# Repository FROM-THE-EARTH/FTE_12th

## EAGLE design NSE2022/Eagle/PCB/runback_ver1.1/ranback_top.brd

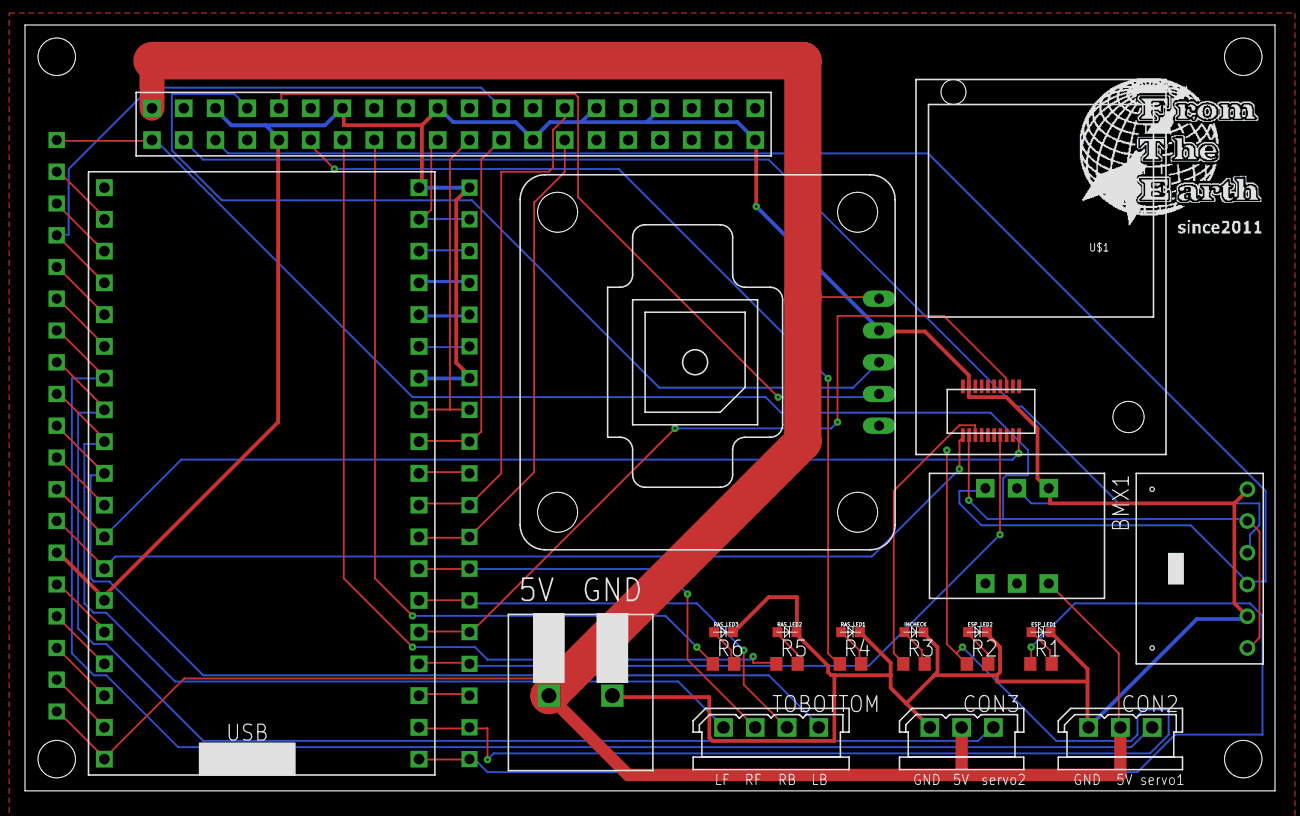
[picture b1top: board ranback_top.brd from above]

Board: 2 copper layers, 100.0 x 61.3 mm, 25 parts (0 on the bottom side), 50 nets.

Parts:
BMX1: BMX055
CON2, CON3: 2.5_MINI-SPOX_3PIN
ESP_LED1, ESP_LED2: OSXX1608C1A
GPS: AE-GYSFDMAXB
IM: IM920C
IMCHECK: OSXX1608C1A
PIN_L: 19_2.54
PIN_R: 19_2.54
R1, R2, R3, R4, R5, R6: 1.5k; R0603
RASPBERRYPI_4B: RASPBERRYPI4B
RAS_LED1, RAS_LED2, RAS_LED3: OSXX1608C1A
TM5: TERMINAL_SLOPED_2PIN
TOBOTTOM: 2.5_MINI-SPOX_4PIN
U$1: LOGO
U$2: ESP32
U$9: GY-BPM280; GY-BMP280-FOOTPRINT

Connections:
+3V3: IM.$P17, PIN_L.1, RASPBERRYPI_4B.3V3_1, U$9.CSB, U$9.VCC
+5V: BMX1.VCC, CON2.2, CON3.2, GPS.P1, PIN_L.19, RASPBERRYPI_4B.5V_1, TM5.1, U$2.5V
BB_SCL: BMX1.SCL, RASPBERRYPI_4B.GPIO3, U$9.SCK
BB_SDA: BMX1.SDA, RASPBERRYPI_4B.GPIO2, U$9.SDI
EN: PIN_L.2, U$2.EN
GND: BMX1.GND, CON2.1, CON3.1, ESP_LED1.CT, ESP_LED2.CT, GPS.P2, IM.$P18, IMCHECK.CT, PIN_L.14, PIN_R.1, PIN_R.7, RASPBERRYPI_4B.GND_1, RASPBERRYPI_4B.GND_2, RASPBERRYPI_4B.GND_3, RASPBERRYPI_4B.GND_4, RASPBERRYPI_4B.GND_5, RASPBERRYPI_4B.GND_6, RASPBERRYPI_4B.GND_7, RASPBERRYPI_4B.GND_8, RAS_LED1.CT, RAS_LED2.CT, RAS_LED3.CT, TM5.2, U$2.GND1, U$2.GND2, U$2.GND3, U$9.GND, U$9.SDO
GPS_RX: GPS.P3, RASPBERRYPI_4B.GPIO14
GPS_TX: GPS.P4, RASPBERRYPI_4B.GPIO15
IM_BUSY: IM.$P1, PIN_L.12, U$2.GPIO14
IM_RESET: IM.$P19, PIN_L.13, U$2.GPIO12
IM_RX: IM.$P6, PIN_R.15, U$2.GPIO2
IM_TX: IM.$P7, PIN_R.16, U$2.GPIO15
IO5: PIN_R.10, U$2.GPIO5
IO8: PIN_R.17, U$2.GPIO8
IO9: PIN_L.16, U$2.GPIO9
IO10: PIN_L.17, U$2.GPIO10
IO11: PIN_L.18, U$2.GPIO11
IO13: PIN_L.15, U$2.GPIO13
IO27: PIN_L.11, U$2.GPIO27
IO34: PIN_L.5, U$2.GPIO34
IO35: PIN_L.6, U$2.GPIO35
LED1: PIN_R.19, R1.1, U$2.GPIO6
LED2: PIN_R.18, R2.1, U$2.GPIO7
LED3: IM.$P15, R3.1
LED4: R4.1, RASPBERRYPI_4B.GPIO17
LED5: R5.1, RASPBERRYPI_4B.GPIO27
LED6: R6.1, RASPBERRYPI_4B.GPIO22
MD_LB: PIN_L.10, TOBOTTOM.P$2, U$2.GPIO26
MD_LF: PIN_L.9, TOBOTTOM.P$1, U$2.GPIO25
MD_RB: PIN_R.14, TOBOTTOM.P$4, U$2.GPIO0
MD_RF: PIN_R.13, TOBOTTOM.P$3, U$2.GPIO4
unnamed: ESP_LED1.AN, R1.2
unnamed: ESP_LED2.AN, R2.2
unnamed: IMCHECK.AN, R3.2
unnamed: R4.2, RAS_LED1.AN
unnamed: R5.2, RAS_LED2.AN
unnamed: R6.2, RAS_LED3.AN
RP_MISO: PIN_R.8, RASPBERRYPI_4B.GPIO9, U$2.GPIO19
RP_MOSI: PIN_R.2, RASPBERRYPI_4B.GPIO10, U$2.GPIO23
RP_RX: PIN_R.11, RASPBERRYPI_4B.GPIO1, U$2.GPIO17
RP_SCK: PIN_R.9, RASPBERRYPI_4B.GPIO11, U$2.GPIO18
RP_SS: PIN_L.4, RASPBERRYPI_4B.GPIO8, U$2.GPIO39
RP_TX: PIN_R.12, RASPBERRYPI_4B.GPIO0, U$2.GPIO16
RXD: PIN_R.4, U$2.TX
SCL: PIN_R.3, U$2.GPIO22
SDA: PIN_R.6, U$2.GPIO21
SENSOR_VP: PIN_L.3, U$2.GPIO36
SERVO1: CON2.3, PIN_L.7, U$2.GPIO32
SERVO2: CON3.3, PIN_L.8, U$2.GPIO33
TXD: PIN_R.5, U$2.RX

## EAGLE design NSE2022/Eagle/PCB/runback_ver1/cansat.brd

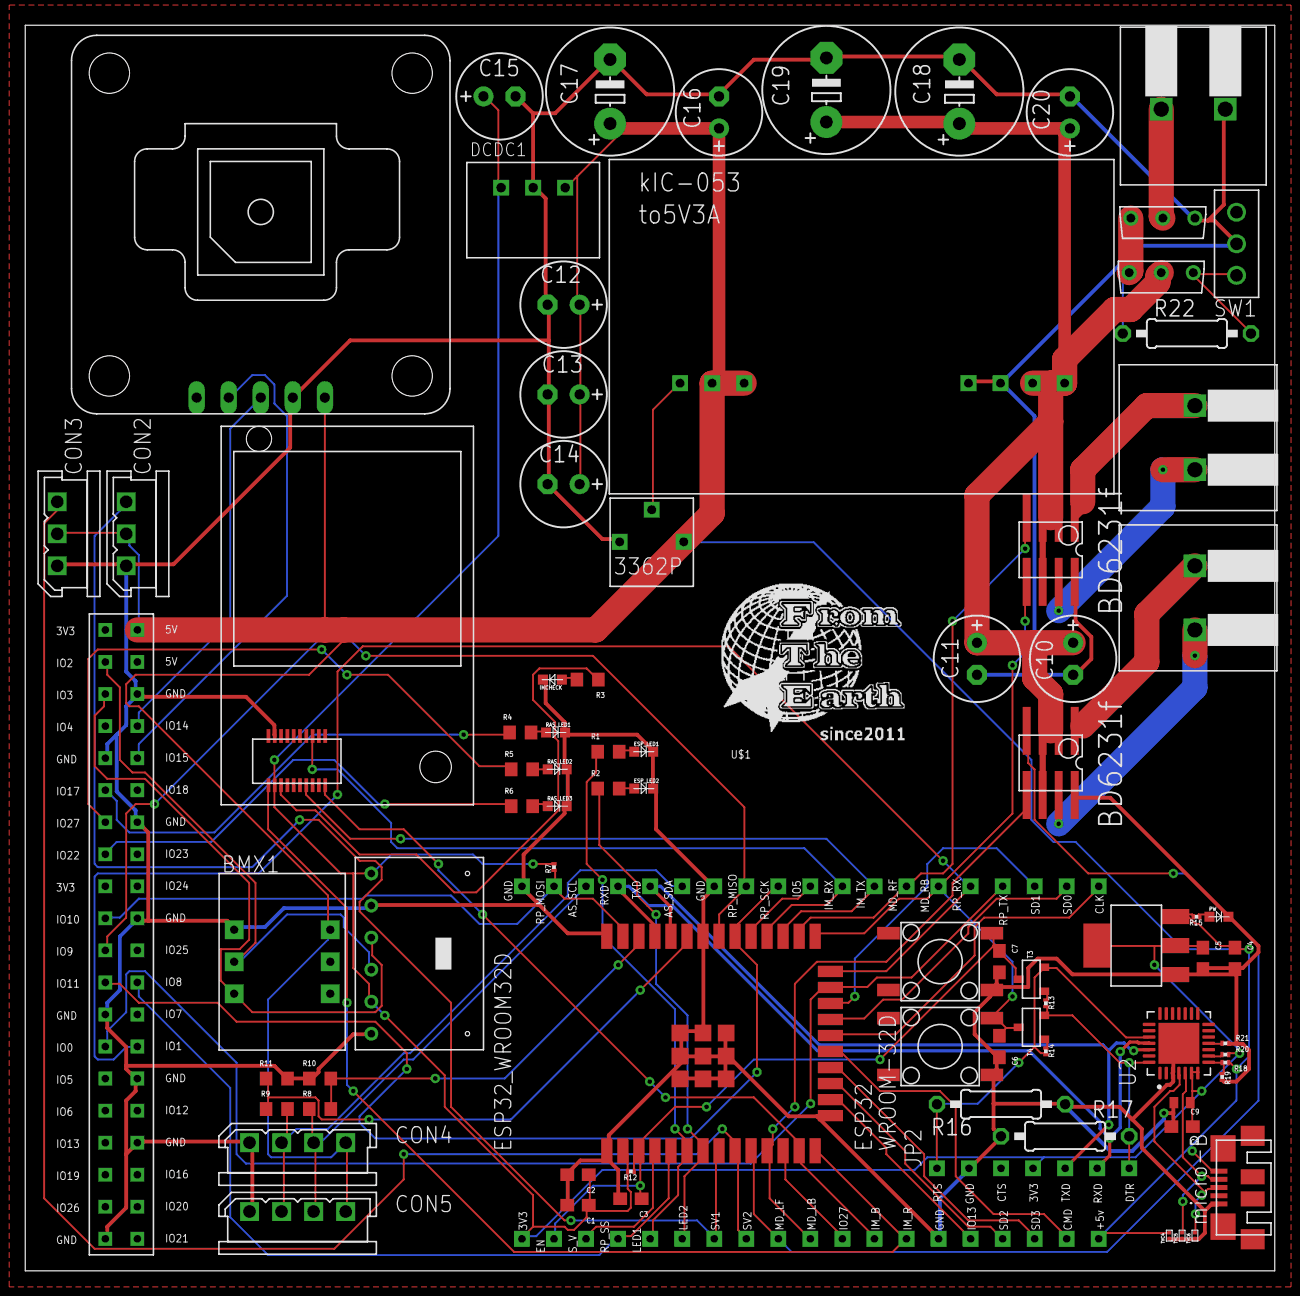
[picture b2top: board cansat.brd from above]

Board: 2 copper layers, 99.0 x 98.7 mm, 84 parts (0 on the bottom side), 71 nets.

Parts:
3-REG2: AZ1117CH-3.3TRG1
100KR1: 100kR; 3362P
BMX1: BMX055
C1: 22uF; C0603
C2, C3, C6, C7, C8: 0.1uF; C0603
C4, C5: 22uf; C0603
C9: 4.7uF; C0402
C10: 100uf; E2,5-7
C11: 0.1uf; E2,5-7
C12, C13, C14, C15: 4.7uF; E2,5-7
C16, C20: 0.1uF; E2,5-7
C17, C18, C19: 1000uF; E5-10,5
CON2, CON3: 2.5_MINI-SPOX_3PIN
CON4, CON5: 2.5_MINI-SPOX_4PIN
DCDC1: 5-3.3; 3.3V0.5A_M78AR05-0.5
EN1: TS-06104
ESP32_WROOM32D: ESP32-WROOM-32D
ESP_LED1, ESP_LED2: OSXX1608C1A
GPS: AE-GYSFDMAXB
IM: IM920C
IMCHECK: OSXX1608C1A
IO1: TS-06104
JP2: 7pin; 7_2.54
MD_L: BD6231F
MD_R: BD6231F
PIN_L: 19_2.54
PIN_R: 19_2.54
PW: OSXX1608C1A
R1, R2, R3, R4, R5, R6: 1.5k; R0603
R7, R12, R13, R14, R21: 10k; R0201
R8, R9: 2.2kR; R0603
R10, R11: 3.3kR; R0603
R15, R20: 2k; R0201
R16, R17: 100k; 0207/10
R18: 22k; R0201
R19: 47k; R0201
R22: 0207/10
RASPBERRYPI_4B: RASPBERRYPI4B
RAS_LED1, RAS_LED2, RAS_LED3: OSXX1608C1A
SW1: SRIDE_SWITCH
T3, T4: NPN_SS8050-G
TM1, TM2, TM3: TERMINAL_SLOPED_2PIN
TVC4, TVC5, TVC6: ESD5484FCT5G
U2: CP2102N-A01-GQFN28; QFN50P500X500X80-29N
U$1: LOGO
U$7, U$10: 2SJ681-PCH; 2SJ681
U$8: 5V3A_KIC-053
U$9: GY-BPM280; GY-BMP280-FOOTPRINT
USB2: MICRO-B_ZX62R-B-5P

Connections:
+3V3: 3-REG2.2, 3-REG2.VOUT, C1.1, C2.1, C5.1, C8.1, C9.1, C15.+, DCDC1.VOUT, ESP32_WROOM32D.2_3V3, IM.$P17, JP2.P$4, PIN_L.P$1, R7.2, R12.2, R20.1, U2.6, U2.7, U$9.CSB, U$9.VCC
+5V: 3-REG2.3, 100KR1.CCW, BMX1.VCC, C4.1, C12.+, C13.+, C14.+, C16.+, C17.+, CON2.2, CON3.2, CON4.P$2, CON5.P$2, DCDC1.VIN, GPS.P1, PIN_L.P$19, R15.2, R18.1, RASPBERRYPI_4B.5V_1, TVC4.2_AN, U$8.VOUT1, U$8.VOUT2, USB2.1
+12V: C10.+, C11.+, C18.+, C19.+, C20.+, MD_L.VCC1, MD_L.VCC2, MD_L.VREF, MD_R.VCC1, MD_R.VCC2, MD_R.VREF, U$8.VIN1, U$8.VIN2, U$10.DRAIN
+D: TVC6.2_AN, U2.4, USB2.3
-D: TVC5.2_AN, U2.5, USB2.2
A7_1: R22.2, U$7.SOURCE, U$10.SOURCE
AS_SCL: CON4.P$4, CON5.P$4, PIN_R.P$3, R8.2
AS_SDA: CON4.P$3, CON5.P$3, PIN_R.P$6, R9.2
BB_SCL: BMX1.SCL, RASPBERRYPI_4B.GPIO3, U$9.SCK
BB_SDA: BMX1.SDA, RASPBERRYPI_4B.GPIO2, U$9.SDI
CLK: ESP32_WROOM32D.20_CLK, PIN_R.P$19
CMD: ESP32_WROOM32D.19_CMD, PIN_L.P$18
CPVBUS: R18.2, R19.2, U2.8
DTR: JP2.P$7, R13.1, R17.2, T4.2, U2.28
EN: C3.1, C7.1, EN1.D, ESP32_WROOM32D.3_EN, PIN_L.P$2, R12.1, T3.3
GND: 3-REG2.1, 100KR1.CW, BMX1.GND, C1.2, C2.2, C3.2, C4.2, C5.2, C6.2, C7.2, C8.2, C9.2, C10.-, C11.-, C12.-, C13.-, C14.-, C15.-, C16.-, C17.-, C18.-, C19.-, C20.-, CON2.1, CON3.1, CON4.P$1, CON5.P$1, DCDC1.GND, EN1.B, ESP32_WROOM32D.1_GND, ESP32_WROOM32D.15_GND, ESP32_WROOM32D.32_NC, ESP32_WROOM32D.38_GND, ESP32_WROOM32D.GND@1, ESP32_WROOM32D.GND@2, ESP32_WROOM32D.GND@3, ESP32_WROOM32D.GND@4, ESP32_WROOM32D.GND@5, ESP32_WROOM32D.GND@6, ESP32_WROOM32D.GND@7, ESP32_WROOM32D.GND@8, ESP32_WROOM32D.GND@9, ESP_LED1.CT, ESP_LED2.CT, GPS.P2, IM.$P18, IMCHECK.CT, IO1.B, JP2.P$2, MD_L.GND, MD_R.GND, PIN_L.P$14, PIN_R.P$1, PIN_R.P$7, PW.CT, R10.1, R11.1, R16.1, R17.1, R19.1, R21.2, RASPBERRYPI_4B.GND_1, RASPBERRYPI_4B.GND_2, RASPBERRYPI_4B.GND_3, RASPBERRYPI_4B.GND_4, RASPBERRYPI_4B.GND_5, RASPBERRYPI_4B.GND_6, RASPBERRYPI_4B.GND_7, RASPBERRYPI_4B.GND_8, RAS_LED1.CT, RAS_LED2.CT, RAS_LED3.CT, SW1.LR, TM3.2, TVC4.1_CT, TVC5.1_CT, TVC6.1_CT, U2.3, U2.29, U$7.GATE, U$8.GND1, U$8.GND2, U$9.GND, U$9.SDO, USB2.5
GPS_RX: GPS.P3, RASPBERRYPI_4B.GPIO14
GPS_TX: GPS.P4, RASPBERRYPI_4B.GPIO15
IM_BUSY: ESP32_WROOM32D.13_IO14, IM.$P1, PIN_L.P$12
IM_RESET: ESP32_WROOM32D.14_IO12, IM.$P19, PIN_L.P$13
IM_RX: ESP32_WROOM32D.28_IO17, IM.$P6, PIN_R.P$11
IM_TX: ESP32_WROOM32D.27_IO16, IM.$P7, PIN_R.P$12
IO5: ESP32_WROOM32D.29_IO5, PIN_R.P$10
IO13: ESP32_WROOM32D.16_IO13, PIN_L.P$15
IO27: ESP32_WROOM32D.12_IO27, PIN_L.P$11
LED1: ESP32_WROOM32D.6_IO34, PIN_L.P$5, R1.1
LED2: ESP32_WROOM32D.7_IO35, PIN_L.P$6, R2.1
LED3: IM.$P15, R3.1
LED4: R4.1, RASPBERRYPI_4B.GPIO17
LED5: R5.1, RASPBERRYPI_4B.GPIO27
LED6: R6.1, RASPBERRYPI_4B.GPIO22
MD_LB: ESP32_WROOM32D.11_IO26, MD_L.RIN, PIN_L.P$10
MD_LF: ESP32_WROOM32D.10_IO25, MD_L.FIN, PIN_L.P$9
MD_RB: C6.1, ESP32_WROOM32D.25_IO0, IO1.D, MD_R.RIN, PIN_R.P$14, T4.3
MD_RF: ESP32_WROOM32D.26_IO4, MD_R.FIN, PIN_R.P$13
unnamed: ESP_LED1.AN, R1.2
unnamed: ESP_LED2.AN, R2.2
unnamed: IMCHECK.AN, R3.2
unnamed: R4.2, RAS_LED1.AN
unnamed: R5.2, RAS_LED2.AN
unnamed: R6.2, RAS_LED3.AN
unnamed: ESP32_WROOM32D.36_IO22, R8.1, R10.2
unnamed: ESP32_WROOM32D.33_IO21, R9.1, R11.2
unnamed: TM3.1, U$7.DRAIN
unnamed: PW.AN, R15.1
unnamed: R13.2, T3.1
unnamed: R14.2, T4.1
unnamed: R20.2, U2.9
unnamed: R21.1, U2.11
unnamed: 100KR1.WIPER, U$8.VADJ
unnamed: R22.1, SW1.L, U$10.GATE
OUT_MD_L1: MD_L.OUT1, TM2.1
OUT_MD_L2: MD_L.OUT2, TM2.2
OUT_MD_R1: MD_R.OUT1, TM1.1
OUT_MD_R2: MD_R.OUT2, TM1.2
RP_MISO: ESP32_WROOM32D.31_IO19, PIN_R.P$8, RASPBERRYPI_4B.GPIO9
RP_MOSI: ESP32_WROOM32D.37_IO23, PIN_R.P$2, R7.1, RASPBERRYPI_4B.GPIO10
RP_RX: ESP32_WROOM32D.24_IO2, PIN_R.P$15, RASPBERRYPI_4B.GPIO1
RP_SCK: ESP32_WROOM32D.30_IO18, PIN_R.P$9, RASPBERRYPI_4B.GPIO11
RP_SS: ESP32_WROOM32D.5_SENSOR_VN, PIN_L.P$4, RASPBERRYPI_4B.GPIO8
RP_TX: ESP32_WROOM32D.23_IO15, PIN_R.P$16, RASPBERRYPI_4B.GPIO0
RTS: JP2.P$1, R14.1, R16.2, T3.2, U2.24
RXD: ESP32_WROOM32D.35_TXD0, JP2.P$6, PIN_R.P$4, U2.25
SD0: ESP32_WROOM32D.21_SD0, PIN_R.P$18
SD1: ESP32_WROOM32D.22_SD1, PIN_R.P$17
SD2: ESP32_WROOM32D.17_SD2, PIN_L.P$16
SD3: ESP32_WROOM32D.18_SD3, PIN_L.P$17
SENSOR_VP: ESP32_WROOM32D.4_SENSOR_VP, PIN_L.P$3
SERVO1: CON2.3, ESP32_WROOM32D.8_IO32, PIN_L.P$7
SERVO2: CON3.3, ESP32_WROOM32D.9_IO33, PIN_L.P$8
TXD: ESP32_WROOM32D.34_RXD0, JP2.P$5, PIN_R.P$5, U2.26

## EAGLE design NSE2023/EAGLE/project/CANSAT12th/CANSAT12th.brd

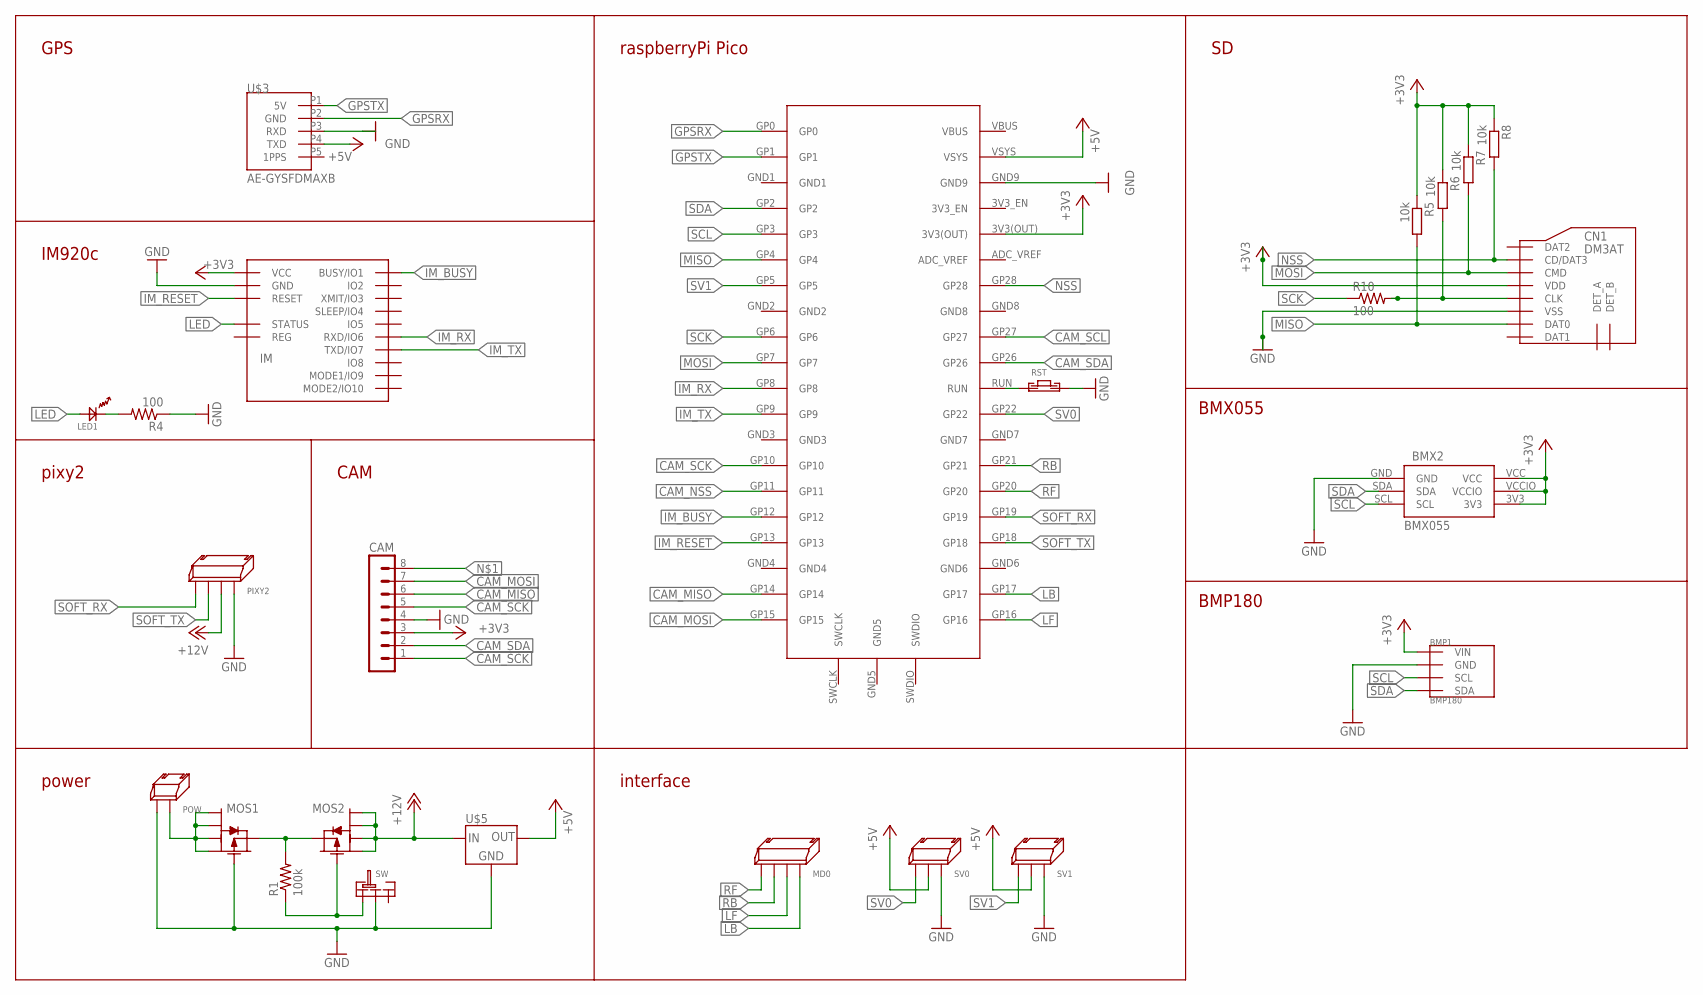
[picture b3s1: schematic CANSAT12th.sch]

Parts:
BMP1: BMP180; GY-68
BMX2: BMX055
CAM: MA08-1
CN1: DM3AT
IM: IM920C
LED1: OSXX1608C1A
MD0: 4PIN_SIDE
MOS1, MOS2: PCH_SSM6J808R; SSM6J808R
PIXY2: 4PIN_SIDE
POW: 2PIN_SIDE
R1: 100k; R0603
R4, R10: 100; R0603
R5, R6, R7, R8: 10k; R0603
RST: TVAF06-A020B-R
SV0, SV1: 3PIN_SIDE
SW: SRIDE_SWITCH
U$1: RASPBERRYPIPICO
U$3: AE-GYSFDMAXB
U$5: LT1117-5; SOT-223

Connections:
+3V3: BMP1.P1 (VIN), BMX2.3V3, BMX2.VCC, BMX2.VCCIO, CAM.3, CN1.VDD, IM.$P17 (VCC), R5.1, R6.1, R7.1, R8.1, U$1.3V3(OUT)
+5V: SV0.P$1, SV1.P$1, U$1.VSYS, U$3.P4 (TXD), U$5.2 (OUT)
+12V: MOS2.1, MOS2.2, MOS2.5, MOS2.6, PIXY2.P$3, U$5.3 (IN)
CAM_MISO: CAM.6, U$1.GP14
CAM_MOSI: CAM.7, U$1.GP15
CAM_NSS: U$1.GP11
CAM_SCK: CAM.1, CAM.5, U$1.GP10
CAM_SCL: U$1.GP27
CAM_SDA: CAM.2, U$1.GP26
GND: BMP1.P2 (GND), BMX2.GND, CAM.4, CN1.VSS, IM.$P18 (GND), MOS1.3, PIXY2.P$4, POW.P$2, R4.1, RST.P$2, SV0.P$3, SV1.P$3, SW.LR, U$5.4 (GND)
GND1: U$3.P3 (RXD)
GPSRX: U$1.GP0, U$3.P2 (GND)
GPSTX: U$1.GP1, U$3.P1 (5V)
IM_BUSY: IM.$P1 (BUSY/IO1), U$1.GP12
IM_RESET: IM.$P19 (RESET), U$1.GP13
IM_RX: IM.$P6 (RXD/IO6), U$1.GP8
IM_TX: IM.$P7 (TXD/IO7), U$1.GP9
LB: MD0.P$4, U$1.GP17
LED: IM.$P15 (STATUS), LED1.AN
LF: MD0.P$3, U$1.GP16
MISO: CN1.DAT0, R5.2, U$1.GP4
MOSI: CN1.CMD, R7.2, U$1.GP7
unnamed: RST.P$1, U$1.RUN
unnamed: LED1.CT, R4.2
unnamed: MOS1.4, MOS2.4, R1.2
unnamed: MOS2.3, R1.1, SW.L
unnamed: MOS1.1, MOS1.2, MOS1.5, MOS1.6, POW.P$1
NSS: CN1.CD/DAT3, R8.2, U$1.GP28
RB: MD0.P$1, U$1.GP21
RF: MD0.P$2, U$1.GP20
SCK: CN1.CLK, R6.2, R10.1, R10.2, U$1.GP6
SCL: BMP1.P3 (SCL), BMX2.SCL, U$1.GP3
SDA: BMP1.P4 (SDA), BMX2.SDA, U$1.GP2
SOFT_RX: PIXY2.P$2, U$1.GP19
SOFT_TX: PIXY2.P$1, U$1.GP18
SV0: SV0.P$2, U$1.GP22
SV1: SV1.P$2, U$1.GP5

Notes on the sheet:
BMP180
BMX055
raspberryPi Pico
GPS
IM920c
pixy2
CAM
power
interface

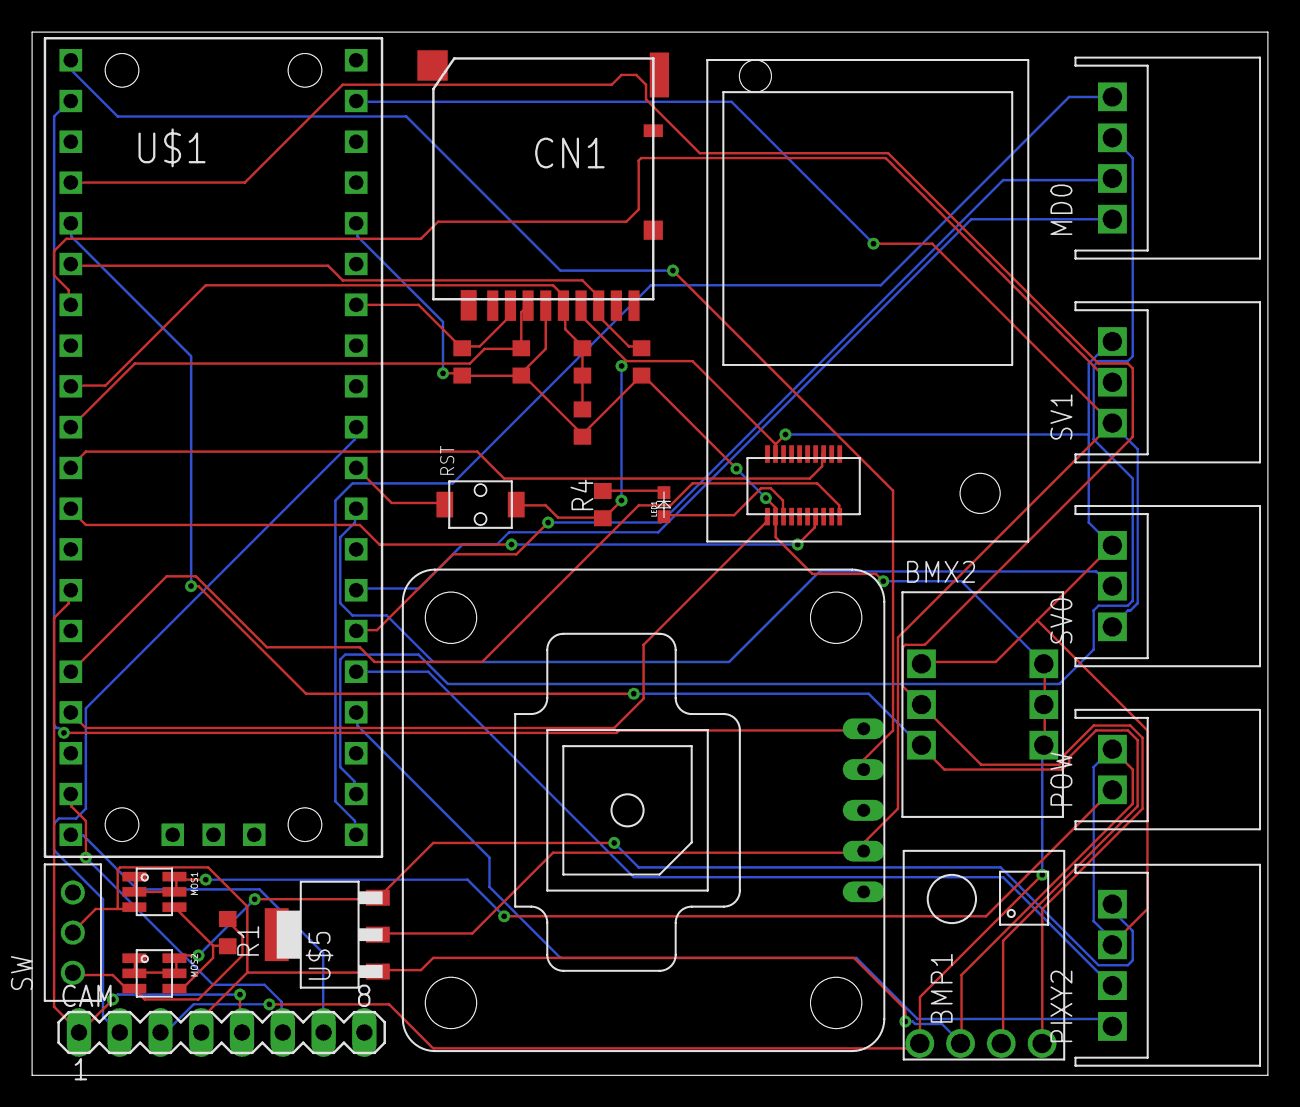
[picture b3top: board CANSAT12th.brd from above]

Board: 2 copper layers, 77.0 x 65.0 mm, 25 parts (0 on the bottom side), 34 nets.

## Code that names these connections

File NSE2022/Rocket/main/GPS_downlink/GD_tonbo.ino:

#include<TinyGPS++.h>
#include<CAN.h>

#include "FS.h"
#include "SD.h"
#include "SPI.h"

TinyGPSPlus gps;
HardwareSerial Serial4(1);
HardwareSerial im920(2);

#define LED1 13
#define LED2 9
#define LED3 10

#define FLIGHT_PIN 32

union BIF {
  uint8_t b[4];
  int i;
  float f;
};

BIF norm;
BIF main_phase;
BIF Altitude;
BIF maxAltitude;
BIF main_val;


const int GPS_RX = 15;
const int GPS_TX = 2;

char buf_lat[20];
char buf_lon[20];

char buf_norm[20];
char buf_Altitude[20];
char buf_maxAltitude[20];
char buf_val[5];
char buf_phase[5];
char buf_time[20];

char logdata[60];
char senddata[40];

double longtitude = 0;
double latitude = 0;

int phase = 0;
int val = 1;
int launchedTime = 0;

bool init_SD = false;
char fileName[16];
int fileNum = 0;

void setup() {

  Serial.begin(115200);
  Serial4.begin(9600, SERIAL_8N1, 2, 15);
  pinMode(FLIGHT_PIN, INPUT);
  im920.begin(19200);
  im920.print("ECIO\r\n");

  CAN.setPins(27, 26);

  if (!CAN.begin(500E3)) {
    Serial.println("Starting CAN failed!");
    int timer = millis();
    while (1) {
      if (millis() - timer > 1000) {
        break;
      }
    }
  }

  if (!SD.begin()) {
    Serial.println("Card Mount Failed");
  } else {
    init_SD = true;
  }

  String s;

  while (1) {

    s = "/LOG";
    if (fileNum < 10) {
      s += "00";
    } else if (fileNum < 100) {
      s += "0";
    }
    s += fileNum;
    s += ".csv";
    s.toCharArray(fileName, 16);
    if (!SD.exists(fileName)) break;
    fileNum++;

  }

  writeFile(SD, fileName, logdata);
}

void loop() {

  while (phase < 4) {
    transmit();
    receive_can();
    val = digitalRead(FLIGHT_PIN);
    if (phase == 1 || phase == 2) {
      sd_write();
    }

    switch (phase) {
      case 0: if (val == 0) {
          launchedTime = millis();
          digitalWrite(LED1, HIGH);
          digitalWrite(LED2, LOW);
          //sd_write();
          phase++;
        } break;

      case 1: if (millis() - launchedTime > 15 * 1000) {
          //case 1:if(maxAltitude.f - Altitude.f > 10){
          digitalWrite(LED1, LOW);
          digitalWrite(LED1, LOW);
          digitalWrite(LED2, HIGH);

          im920.print("para_open");
          //sd_write();
          phase++;
        } break;

      case 2: if (millis() - launchedTime > 180 * 1000) {
          digitalWrite(LED1, LOW);
          digitalWrite(LED2, LOW);

          phase++;
        } break;

    }
  }

}

void transmit() {


  if (Serial4.available() > 0) {
    char c = Serial4.read();
    gps.encode(c);

    if (gps.location.isUpdated()) {
      //Serial.print("LAT: ");Serial.println(gps.location.lat(),9);
      //Serial.print("LONG: ");Serial.println(gps.location.lng(),9);


      longtitude = gps.location.lng();
      latitude = gps.location.lat();

      dtostrf(longtitude, 8, 10, buf_lon);
      dtostrf(latitude, 8, 10, buf_lat);

      dtostrf(norm.f, 5, 2, buf_norm);
      dtostrf(Altitude.f, 5, 2, buf_Altitude);
      dtostrf(maxAltitude.f, 5, 2, buf_maxAltitude);

      sprintf(buf_val, "%d", val);
      sprintf(buf_time, "%d", millis() - launchedTime);
      //buf_val = char(main_val.i);
      //buf_phase = char(main_phase.i);

      char b_val[10];
      sprintf(b_val, "%d", val);

      sprintf(senddata, "ECIO\r\nTXDA %s,%s,%s,%s,%s,%s,%s,%s\r\n", buf_lat, buf_lon, buf_Altitude, b_val, buf_val, buf_norm, buf_maxAltitude, buf_phase);
      sprintf(logdata, "%s,%s,%s,%s\r\n", buf_time, buf_lon, buf_lat, buf_val);

      im920.print(senddata);

    } else {
      Serial.println("GPS_ERROR");

      dtostrf(longtitude, 9, 6, buf_lon);
      dtostrf(latitude, 9, 6, buf_lat);

      dtostrf(norm.f, 5, 4, buf_norm);
      dtostrf(Altitude.f, 5, 4, buf_Altitude);
      dtostrf(maxAltitude.f, 5, 4, buf_maxAltitude);

      //buf_phase = char(main_phase.i);

      sprintf(buf_val, "%d", val);
      sprintf(buf_phase, "%d", main_phase.i);
      sprintf(buf_time, "%d", millis() - launchedTime);

      char bu_val[10];
      sprintf(bu_val, "%d", val);

      sprintf(senddata, "ECIO\r\nTXDA %s,%s,%s,%s,%s,%s,%s,%s\r\n", buf_lat, buf_lon, buf_Altitude, bu_val, buf_val, buf_norm, buf_maxAltitude, buf_phase);
      sprintf(logdata, "%s,%s,%s,%s\r\n", buf_time, buf_lon, buf_lat, buf_val);


      im920.print(senddata);

      Serial.println("send");

      delay(500);


    }
  }

}


void receive_can() {

  int timer = 0;
  int packetSize = CAN.parsePacket();

  if (packetSize) {
    Serial.print("Received ");

    if (CAN.packetExtended()) {
      Serial.print("extended ");
    }

    if (CAN.packetRtr()) {

      Serial.print("RTR ");
    }

    byte id = CAN.packetId();
    Serial.print("packet with id 0x");
    Serial.print(id, HEX);

    if (CAN.packetRtr()) {
      Serial.print(" and requested length ");
      Serial.println(CAN.packetDlc());
    } else {

      Serial.print(" and length ");
      Serial.println(packetSize);

      if (CAN.available()) {

        if (id == 18) {
          norm.b[0] = CAN.read();
          norm.b[1] = CAN.read();
          norm.b[2] = CAN.read();
          norm.b[3] = CAN.read();
          Serial.println(norm.f);
        } else if (id == 16) {
          Altitude.b[0] = CAN.read();
          Altitude.b[1] = CAN.read();
          Altitude.b[2] = CAN.read();
          Altitude.b[3] = CAN.read();
          Serial.println(Altitude.f);
        } else if (id == 192) {
          maxAltitude.b[0] = CAN.read();
          maxAltitude.b[1] = CAN.read();
          maxAltitude.b[2] = CAN.read();
          maxAltitude.b[3] = CAN.read();
          Serial.println(maxAltitude.f);
        } else if (id == 17) {
          main_phase.b[0] = CAN.read();
          main_phase.b[1] = CAN.read();
          Serial.println(main_phase.i);
        } else if (id == 193) {
          main_val.b[0] = CAN.read();
          main_val.b[1] = CAN.read();
          Serial.println(main_val.i);
        } else {
          Serial.println("EROOR");
        }

      }
      //Serial.println(norm.f);
    }

    Serial.println();
  }

}

void sd_write() {

  appendFile(SD, fileName, logdata);
}

void writeFile(fs::FS &fs, const char * path, const char * message) { //to write first information to the new file
  Serial.printf("Writing file: %s\n", path);

  File file = fs.open(path, FILE_WRITE);
  if (!file) {
    Serial.println("Failed to open file for writing");
    return;
  }
  if (file.print(message)) {
    Serial.println("File written");
  } else {
    Serial.println("Write failed");
  }
  file.close();
}

//use to append information to SD
void appendFile(fs::FS &fs, const char * path, const char * message) { //to add information to the previous file
  Serial.printf("Appending to file: %s\n", path);

  File file = fs.open(path, FILE_APPEND);

  if (!file) {
    Serial.println("Failed to open file for appending");
    return;
  }
  if (file.print(message)) {
    Serial.println("Message appended");
  } else {
    Serial.println("Append failed");
  }
  file.close();
}
